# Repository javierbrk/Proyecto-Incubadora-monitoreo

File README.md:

# LibrePollo

Is an innovative project aimed at enhancing the efficiency and productivity of poultry incubators in family farming. Developed by Asociación Civil AlterMundi and CTO, this system integrates advanced monitoring and control technologies to optimize temperature and humidity levels, reducing manual labor and increasing hatch rates. Utilizing free hardware and software, the project promotes sustainable agricultural practices and empowers local communities with technical skills. Join us in revolutionizing family farming with technology!

## made with :heart: by:

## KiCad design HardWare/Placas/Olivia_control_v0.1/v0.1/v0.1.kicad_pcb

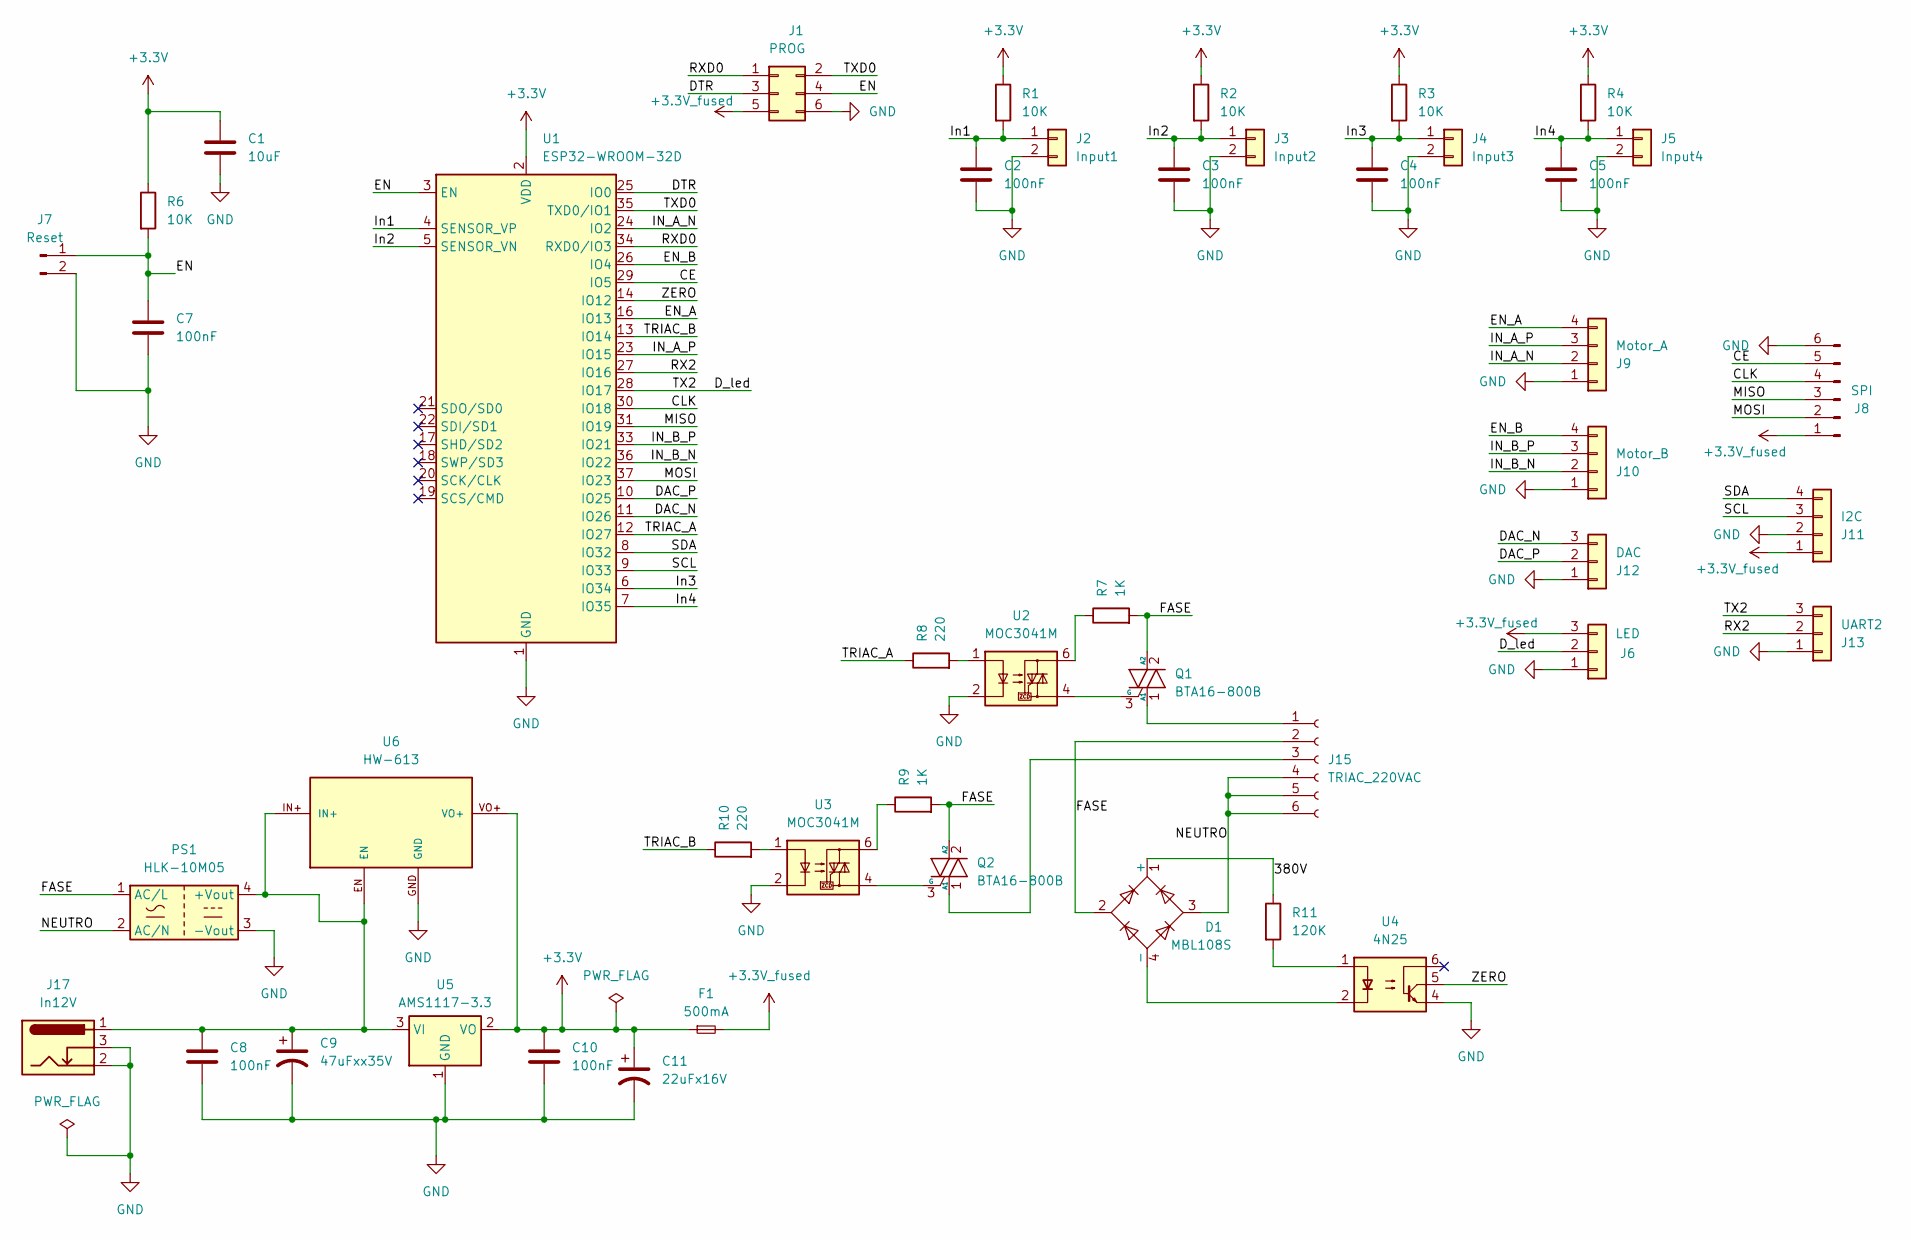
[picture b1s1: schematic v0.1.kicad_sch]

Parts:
C1: 10uF; C_0805_2012Metric_Pad1.18x1.45mm_HandSolder
C2, C3, C4, C5, C7, C8, C10: 100nF; C_0805_2012Metric_Pad1.18x1.45mm_HandSolder
C9: 47uFxx35V; CP_EIA-6032-28_Kemet-C_Pad2.25x2.35mm_HandSolder
C11: 22uFx16V; CP_EIA-6032-28_Kemet-C_Pad2.25x2.35mm_HandSolder
D1: MBL108S; Diode_Bridge_Vishay_DFS
F1: 500mA; Fuse_1206_3216Metric_Pad1.42x1.75mm_HandSolder
J1: PROG; PinHeader_2x03_P2.54mm_Vertical
J2: Input1; Molex_SL_171971-0002_1x02_P2.54mm_Vertical
J3: Input2; Molex_SL_171971-0002_1x02_P2.54mm_Vertical
J4: Input3; Molex_SL_171971-0002_1x02_P2.54mm_Vertical
J5: Input4; Molex_SL_171971-0002_1x02_P2.54mm_Vertical
J6: LED; Molex_SL_171971-0003_1x03_P2.54mm_Vertical
J7: Reset; PinHeader_1x02_P2.54mm_Vertical
J8: SPI; PinHeader_1x06_P2.54mm_Vertical
J9: Motor_A; Molex_SL_171971-0004_1x04_P2.54mm_Vertical
J10: Motor_B; Molex_SL_171971-0004_1x04_P2.54mm_Vertical
J11: I2C; Molex_SL_171971-0004_1x04_P2.54mm_Vertical
J12: DAC; Molex_SL_171971-0003_1x03_P2.54mm_Vertical
J13: UART2; Molex_SL_171971-0003_1x03_P2.54mm_Vertical
J15: TRIAC_220VAC; Molex_Mini-Fit_Jr_5569-06A2_2x03_P4.20mm_Horizontal
J17: In12V; BarrelJack_Horizontal
PS1: HLK-10M05; Converter_ACDC_Hi-Link_HLK-10Mxx
Q1, Q2: BTA16-800B; TO-220-3_Vertical
R1, R2, R3, R4, R6: 10K; R_0805_2012Metric_Pad1.20x1.40mm_HandSolder
R7, R9: 1K; R_0805_2012Metric_Pad1.20x1.40mm_HandSolder
R8, R10: 220; R_0805_2012Metric_Pad1.20x1.40mm_HandSolder
R11: 120K; R_0805_2012Metric_Pad1.20x1.40mm_HandSolder
U1: ESP32-WROOM-32D
U2, U3: MOC3041M; SMDIP-6_W9.53mm
U4: 4N25; SMDIP-6_W9.53mm
U5: AMS1117-3.3; SOT-223-3_TabPin2
U6: HW-613

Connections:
+3.3V: C1.1, C10.1, C11.1, F1.1, R1.1, R2.1, R3.1, R4.1, R6.1, U1.2 (VDD), U5.2 (VO), U6.VO+; also elsewhere on the board
+3.3V_fused: F1.2, J1.5, J6.3, J8.1, J11.1
/380V: D1.1 (+), R11.1
/CE: J8.5, U1.29 (IO5)
/CLK: J8.4, U1.30 (IO18)
/DAC_N: J12.3, U1.11 (IO26)
/DAC_P: J12.2, U1.10 (IO25)
/DTR: J1.3, U1.25 (IO0); also elsewhere on the board
/D_led: J6.2, J13.3, U1.28 (IO17)
/EN: C7.1, J1.4, J7.1, R6.2, U1.3 (EN)
/EN_A: J9.4, U1.16 (IO13)
/EN_B: J10.4, U1.26 (IO4)
/FASE: D1.2, J15.2, PS1.1 (AC/L), Q1.2 (A2), Q2.2 (A2), R7.2, R9.2
/IN_A_N: J9.2, U1.24 (IO2)
/IN_A_P: J9.3, U1.23 (IO15)
/IN_B_N: J10.2, U1.36 (IO22)
/IN_B_P: J10.3, U1.33 (IO21)
/In1: C2.1, J2.1, R1.2, U1.4 (SENSOR_VP)
/In2: C3.1, J3.1, R2.2, U1.5 (SENSOR_VN)
/In3: C4.1, J4.1, R3.2, U1.6 (IO34)
/In4: C5.1, J5.1, R4.2, U1.7 (IO35)
/MISO: J8.3, U1.31 (IO19)
/MOSI: J8.2, U1.37 (IO23)
/NEUTRO: D1.3, J15.4, J15.5, J15.6, PS1.2 (AC/N)
/RX2: J13.2, U1.27 (IO16)
/RXD0: J1.1, U1.34 (RXD0/IO3)
/SCL: J11.3, U1.9 (IO33)
/SDA: J11.4, U1.8 (IO32)
/TRIAC_A: R8.1, U1.12 (IO27)
/TRIAC_B: R10.1, U1.13 (IO14)
/TXD0: J1.2, U1.35 (TXD0/IO1)
/ZERO: U1.14 (IO12), U4.5
GND: C1.2, C2.2, C3.2, C4.2, C5.2, C7.2, C8.2, C9.2, C10.2, C11.2, J1.6, J2.2, J3.2, J4.2, J5.2, J6.1, J7.2, J8.6, J9.1, J10.1, J11.2, J12.1, J13.1, J17.2, J17.3, PS1.3 (-Vout), U1.1 (GND), U1.15 (GND), U1.38 (GND), U1.39 (GND), U2.2, U3.2, U4.4, U5.1 (GND), U6.GND
unnamed: D1.4 (-), U4.2
unnamed: J15.1, Q1.1 (A1)
unnamed: J15.3, Q2.1 (A1)
unnamed: C8.1, C9.1, J17.1, PS1.4 (+Vout), U5.3 (VI), U6.EN, U6.IN+
unnamed: Q1.3 (G), U2.4
unnamed: Q2.3 (G), U3.4
unnamed: R7.1, U2.6
unnamed: R8.2, U2.1
unnamed: R9.1, U3.6
unnamed: R10.2, U3.1
unnamed: R11.2, U4.1

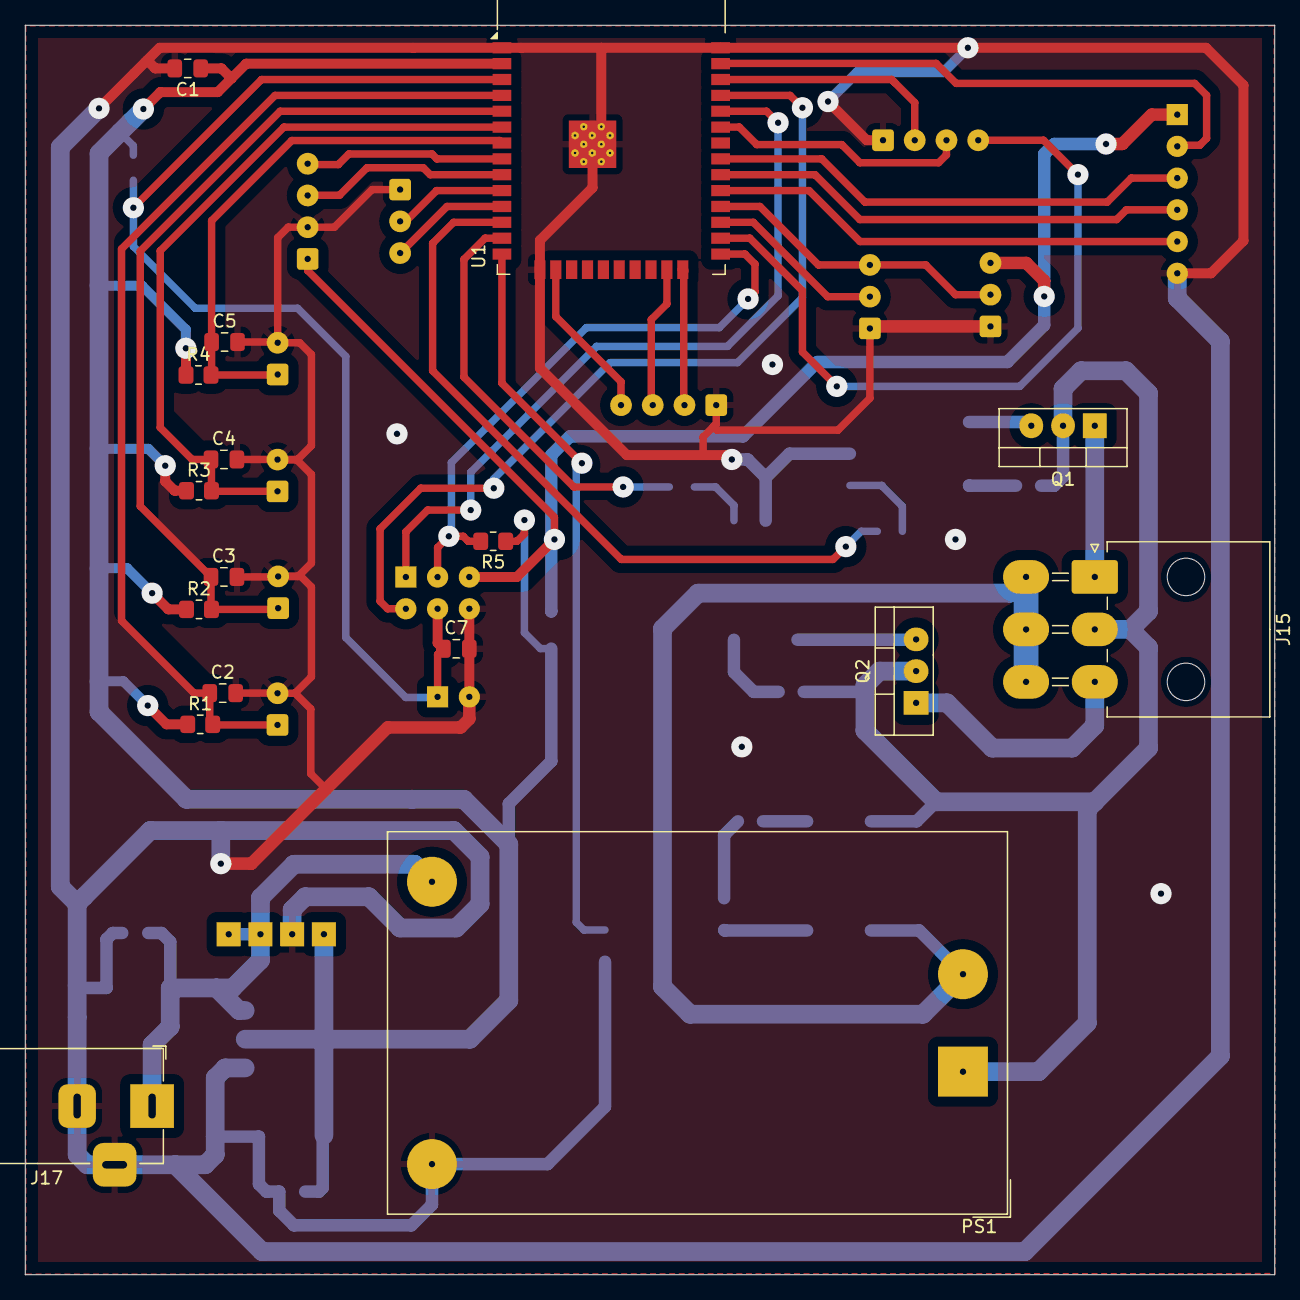
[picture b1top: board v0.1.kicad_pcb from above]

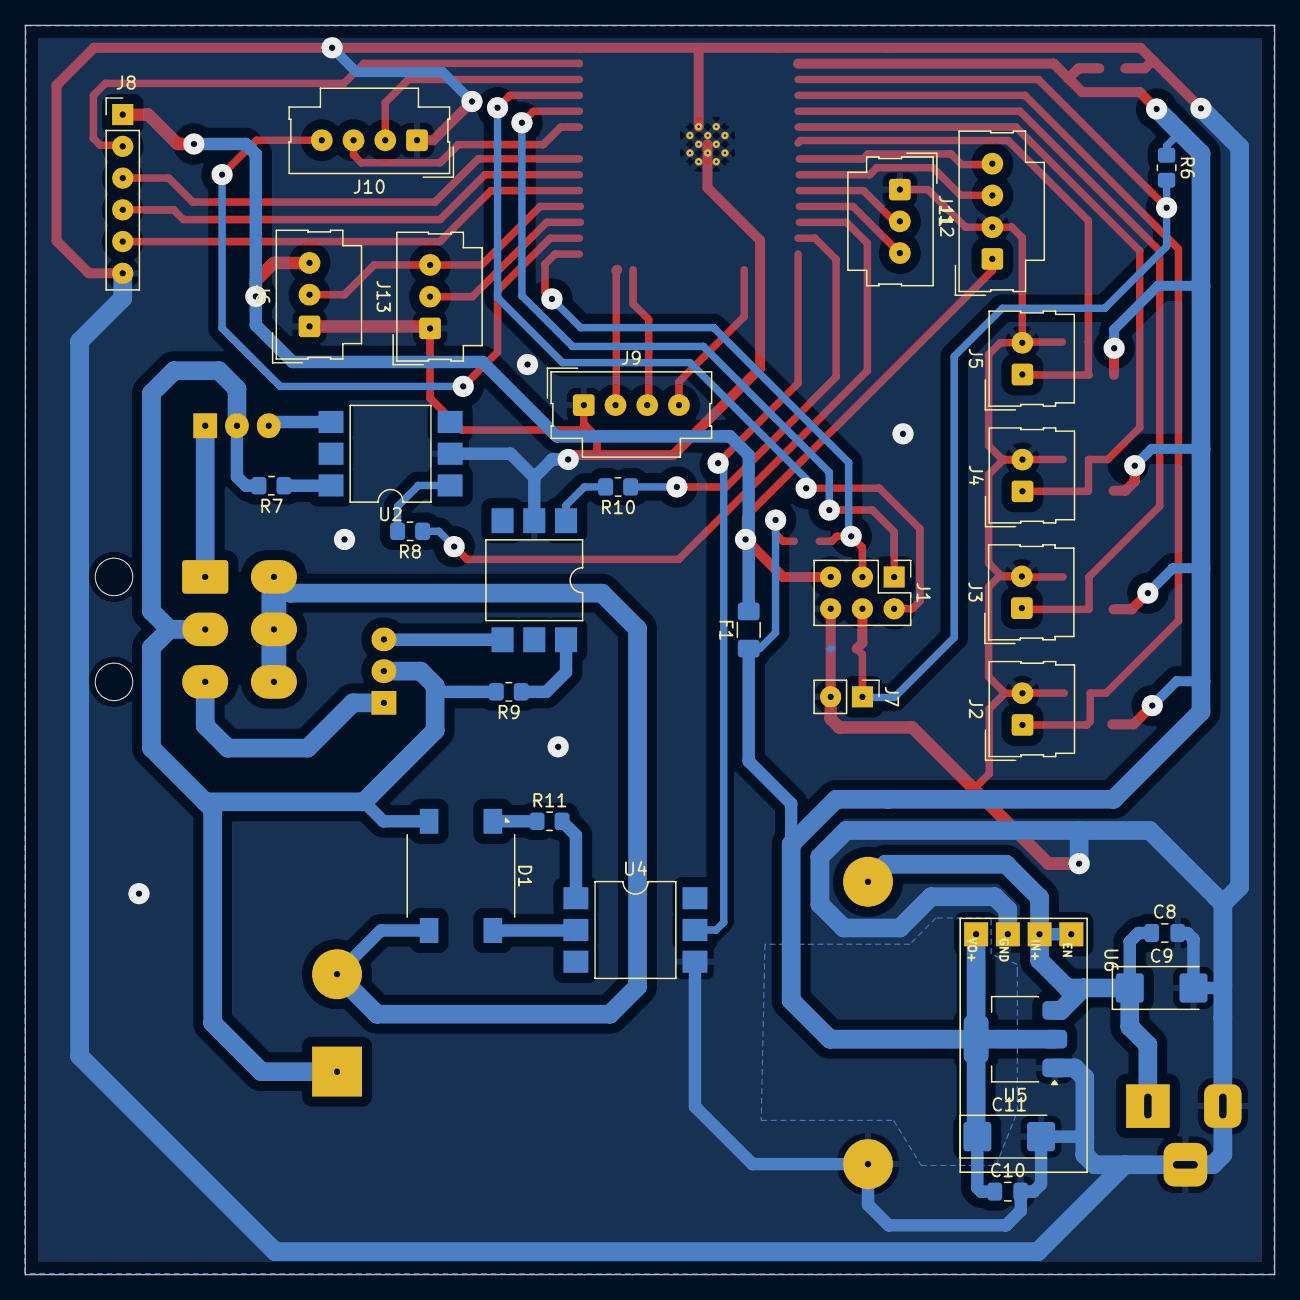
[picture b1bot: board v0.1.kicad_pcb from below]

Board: 2 copper layers, 100.0 x 100.0 mm, 47 parts (30 on the bottom side), 44 nets.

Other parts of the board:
R5: 10K; R_0805_2012Metric_Pad1.20x1.40mm_HandSolder

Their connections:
+3.3V: R5.1; also elsewhere on the board
/DTR: R5.2; also elsewhere on the board

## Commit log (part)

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2024-04-19 Fix old rest api(only GET methods)
2024-04-19 copied lib folder
2024-04-19 removed and ignored files
2024-04-19 added updated config_model file
2024-04-26 Add WiFi Manager for new connections.
2024-05-01 Add corrections required
2024-05-01 Remove _G[W] = W line
2024-05-04 Add humidifier STL files
2024-05-07 added post in configurations view Fixes #29
2024-05-10 updated api
2024-05-31 configurations view shows the elapsed time since the tray buttons were pressed
2024-06-07 Add Tubo_Humidificador.stl
2024-06-07 triac: first atempt
2024-06-07 triac: seccond attempt
2024-06-19 added readme
2024-06-19 changes to readme
2024-06-19 readme added to harware and software
2024-06-25 the buttons keep their colors Fixes #52
2024-06-26 added notifications view
2024-06-28 readme files changed
2024-06-28 link to PAD INCUBADORA updated
2024-07-08 changes in grafana view
2024-07-10 new version based on the new gpio api
2024-07-10 add submodule
2024-07-10 Add binaries for ESP32-CAM
2024-07-12 changes in config view
2024-07-15 placa Olivia v0.1 esquematico
2024-07-17 pcb primer borrador
2024-07-17 pcb primera version
2024-07-18 pcb fix Io0 pull-up
2024-07-18 minor fix routing
2024-07-19 various fix. Traces:0,5. Clearance:1,0
2024-07-19 reduce esp pad size
2024-07-20 minor fix
2024-07-24 Add WiFi Handler
2024-07-26 Test Fabri Config
2024-07-29 Revert "Test Fabri Config"
    This reverts commit b485b1999be309a7c12906e24227fa8b9d2a6b47.
2024-07-29 fixes tests
2024-07-29 fixes last two tests
2024-07-31 implements humidity control
2024-07-31 fix pin number and inicializations
2024-08-02 fixes gpio issue
2024-08-02 fixes triac function
2024-08-02 fix grafana logs
2024-08-02 add aninit
2024-08-02 adds beter log
2024-08-02 fix to string
2024-08-02 disable simul
2024-08-03 implements warn messages
2024-08-05 fixes time dependency
2024-08-05 adds ods test reference
2024-08-09 humidity fields in configuration
2024-08-30 fixes #77
2024-08-30 changes onofftime
2024-08-30 first atept
2024-08-30 impement tests
2024-09-03 Replace prints for logs and logs only send if is type error
2024-09-03 fix gpio numer error
2024-09-03 minor fixes
2024-09-05 Fix API and some minor bugs
2024-09-11 add requested changes
2024-09-19 Smaller more compact layout with AC restriction zone.
2024-10-03 volteo 2.0.1
2024-10-07 fixes rotation initiation when sensor is active
2024-10-11 Add log module in wifiinit
2024-10-11 f_rotation: improves messages and prevents noisi activations
2024-10-11 f_rotation: cleanup ready
2024-10-18 New humidifier logic
2024-10-21 fix_controler
2024-10-21 fix incubator time
2024-10-22 Fix TDD and incubator
2024-10-25 rotation STL files added
2024-10-25 pull request and reomte repo script
2024-10-25 getpullrequest.sh instructions
2024-10-25 fixed variable in credentials.lua
2024-10-28 data adapted to fw
2024-11-01 fixes for integration
2024-11-01 fixed api
2024-11-04 Add new field 'wifi_status'
2024-11-04 Update restapi.lua
    use connected and disconnected
2024-11-04 Fix new field logic 'wifi.ONLINE'
2024-11-04 Fix minors changes in wifiinit
2024-11-06 Fix Incubator name with MAC
2024-11-06 Fix changes requested
2024-11-07 Update incubatorController.lua
    do not disable rotation unless one of the sensors is down
2024-11-07 improves rotation failure detection
2024-11-10 Fix wifi scan function
2024-11-12 fixcredentials
2024-11-12 changed ip for esp
2024-11-13 Update incubatorController.lua
    Deshacer comentario de los timers
2024-11-15 fixes after real tests
2024-11-24 added fitted box for actual values + scroll in config view
2024-11-28 agregado de lista de componentes de incubadora
2024-11-29 added updated actual model
2024-12-01 Remuevo carpetas de otras placas
    Retiro del repo las carpetas de los prototipos anteriores
2024-12-01 Create esquemaLibreIncu
    Genero el archivo con algunos componentes del esquema eléctrico
2024-12-02 Actualizo con mejoras el esquema
2024-12-02 Más mejoras en el esquema
2024-12-02 creo PuenteH y Modulo relé
2024-12-02 add 10 more characters in hash and incubator_name
2024-12-02 add TDD for new commit
2024-12-02 add equal symbol missing
2024-12-02 add time(s) for web requests tdd
2024-12-03 corrijo elementos y avanzo con conexiones
2024-12-04 newpost
2024-12-05 implements ds sensor readings
2024-12-05 implement ds sensors in incubator controller
2024-12-06 only wait for a sensor if a sensor was on...
2024-12-10 integration
2024-12-10 disablemessages
2024-12-11 Add Improves in to wifiinit
2024-12-12 Add follow of state and temporixer
2024-12-16 Add Allow empty passwd
2024-12-16 Add new incubator name (MAC)
2025-01-03 new logic for wifi connection
2025-01-07 remove unwated error messages, change them for a warning
2025-01-09 rest api: add rotation api
2025-01-09 rotation api: fix req error and add consistent error handling
2025-01-09 fix wifi, online status
2025-01-09 fixes status report
2025-01-09 reenable rest api server
2025-01-09 add post for rotation
2025-01-09 connection to open networks is now available
2025-01-09 improved initial home
2025-01-09 fixes rotation interval
2025-01-09 fixes #170
2025-01-10 fixes incubator name
2025-01-10 set rotation duration to 3 secconds more than the maximum rotation time
2025-01-10 fix resitor initial value
2025-01-10 refactor WiFi initialization and connection handling; improve logging and ensure unique SSID ignore credentials file support for infinite reconect
2025-01-10 update incubator name format to include 'incu-' prefix and remove colons from MAC address
2025-01-10 refactor logging mechanism to use log.addError for error handling; improve error tracking for temperature, humidity, rotation, and WiFi issues
2025-01-11 refactor error logging in temperature and humidity controls; improve alert messages and formatting
2025-01-11 remove Grafana alerts, add time stamp to error message
2025-01-11 fix: correct formatting in temperature logging and adjust alert cycle count
2025-01-11 refactor: replace Grafana alerts with log.addError for temperature condition checks
2025-01-11 reset resistor counter and improve error text
2025-01-11 simplify and make more deterministic resistor and humidity control logic; improve error logging
2025-01-11 fix: adjust temperature threshold for resistor alarm, temperature changes are really slow
2025-01-24 several aesthetic changes
2025-01-27 hardcoded values
2025-01-29 fix timer inicialization error in incubatorController.lua
    [34m[TRACE 2025-01-29 12:48:15 DST:0] [0m : Sending data to Grafana
    [34m[TRACE 2025-01-29 12:48:15 DST:0] [0m : [R] Setting rotation duration to 66266.1
    incubatorController.lua:315: bad argument #1 to 'register' (Range: 1-6870947)
    stack traceback:
    [C]: in function 'register'
    incubatorController.lua:315: in function <incubatorController.lua:294>
2025-02-01 shows ap notifications/alerts
2025-02-02 functioning manual rotation buttons
2025-02-03 Update incubator.lua
    fix time between successive humidifier turn on
2025-02-03 add notify meesages
    add Jere's pull request #158 code without format modifications and with hard-coded url
2025-02-03 Update log.lua
    fix function name
2025-02-04 reduce rotation period and calify comments
2025-02-04 fix initial temp problem
2025-02-05 implement derivatives and smoothnes
2025-02-05 set default parameters
2025-02-05 add gpio status
2025-02-05 prevent false positves in temp changes
2025-02-05 add delay to rotate
2025-02-05 remove "bme" text
2025-02-05 cosmetics
2025-02-05 mejoras en el esquema eléctrico
2025-02-05 Create LICENSE
2025-02-05 add spdx license to all files
2025-02-07 fix default temp
2025-02-07 fix multiple false positives at start
2025-02-07 add temperature to low
2025-02-09 new logic to show grafana panels
2025-02-09 added icon and name to the app
2025-02-09 takes the name from hash instead of incubator_name
2025-02-11 fixes #186
2025-02-11 fixes bug in wifi
2025-02-11 fix false positives
2025-02-11 use hash to avoid grafana board data overlap
2025-02-13 tutorial on how to subscribe to ntfy
2025-02-14 limits the amount of posts from the rotation arrows
2025-03-14 final 3d models for rotation
